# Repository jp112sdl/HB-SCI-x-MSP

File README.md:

# HB-SCI-x-MSP

Ultra-Low-Power 1...4-fach Schließerkontakt-Interface _(basiert auf HM-SCI-3-FM mit MSP430(F2001) Kontaktüberwachung)_.

https://user-images.githubusercontent.com/18190139/149153497-77211921-73f8-495d-b231-c35b709c72b2.mp4

- Code für den MSP430: [main.c](https://github.com/jp112sdl/HB-SCI-x-MSP/blob/master/TI_MSP430/main.c)
- Code für den AVR: [MSP430State.h](https://github.com/jp112sdl/HB-SCI-x-MSP/blob/master/MSP430State.h) und [HB-SCI-x-MSP.ino](https://github.com/jp112sdl/HB-SCI-x-MSP/blob/master/HB-SCI-x-MSP.ino)
  - benötigte Libs: 
    - [Low-Power](https://github.com/rocketscream/Low-Power/)
    - [EnableInterrupt](https://github.com/GreyGnome/EnableInterrupt/)
    - [AskSinPP](https://github.com/pa-pa/AskSinPP)

#### Schaltplan

#### Platine (57x24mm)

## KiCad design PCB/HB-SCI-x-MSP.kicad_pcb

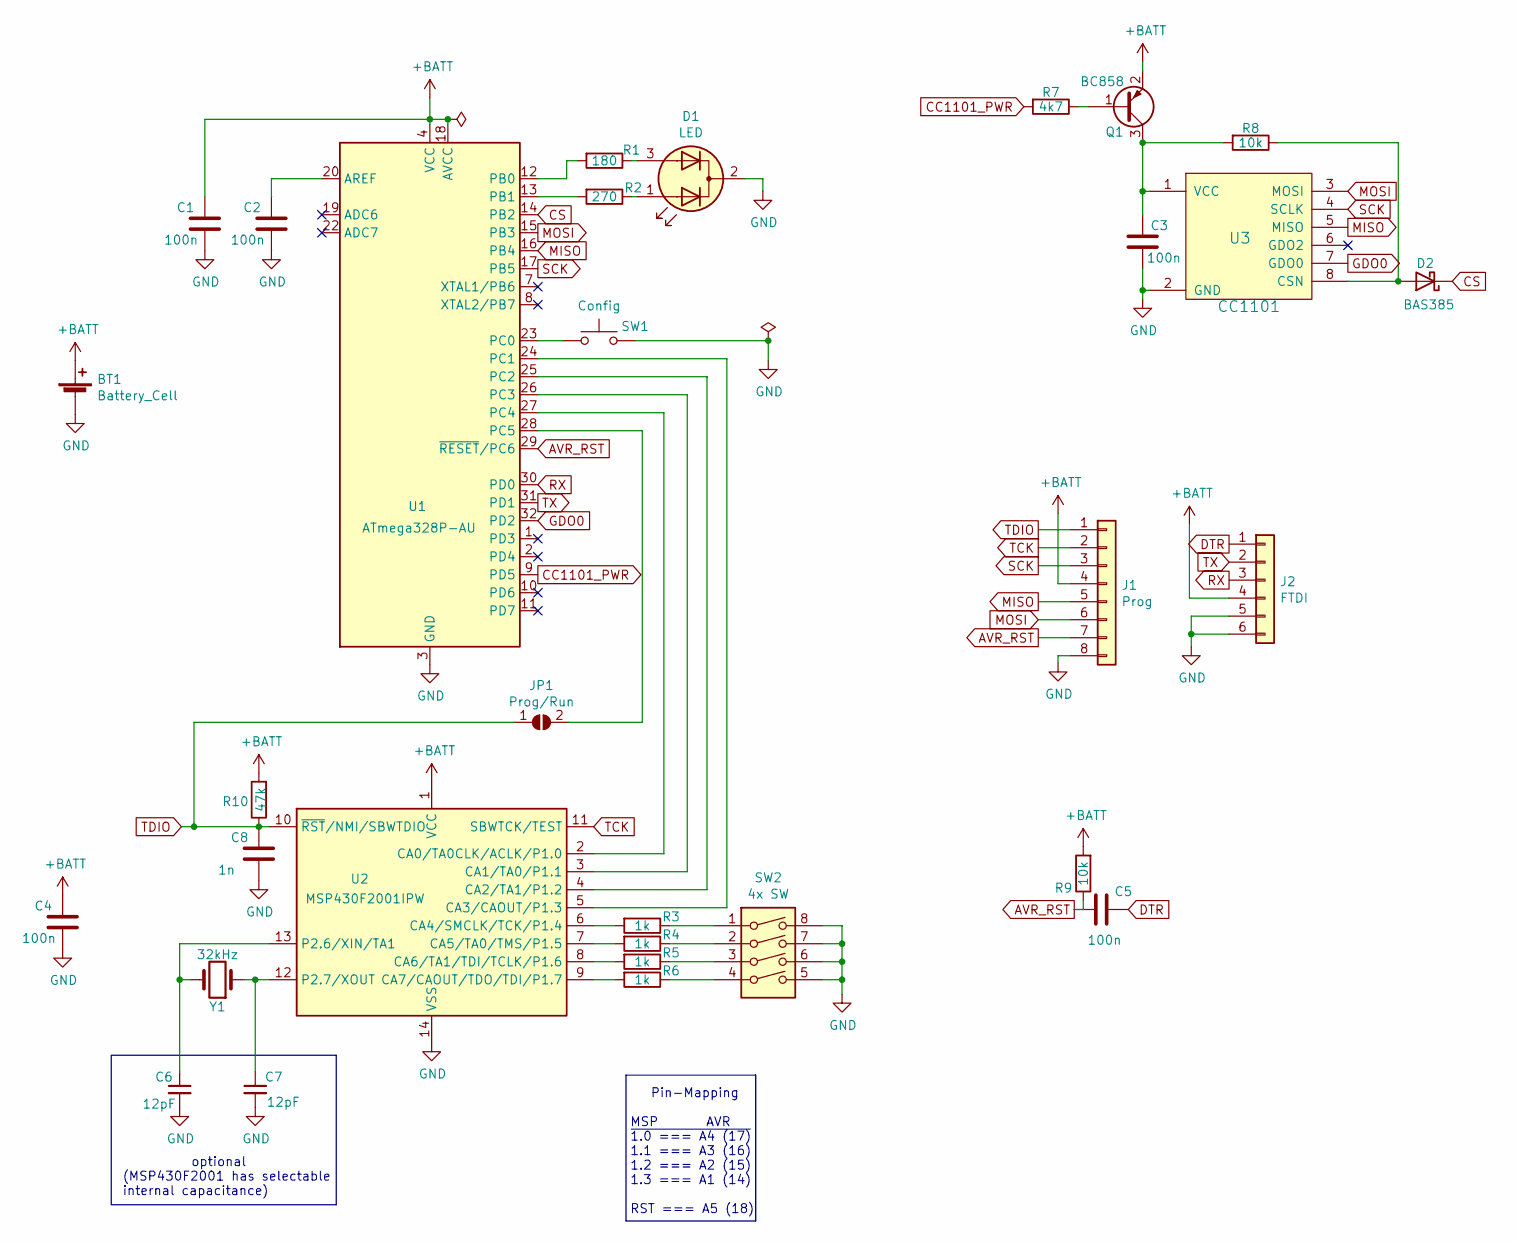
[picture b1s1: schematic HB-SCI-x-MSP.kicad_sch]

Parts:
BT1: Battery_Cell; BatteryHolder_Keystone_1060_1x2032
C1, C2, C3, C4, C5: 100n; C_0805_2012Metric_Pad1.15x1.40mm_HandSolder
C6, C7: 12pF; C_0805_2012Metric_Pad1.15x1.40mm_HandSolder
C8: 1n; C_0805_2012Metric_Pad1.15x1.40mm_HandSolder
D1: LED; LED_D3.0mm-3
D2: BAS385; D_MicroMELF_Hadsoldering
J1: Prog; PinHeader_1x08_P2.00mm_Vertical
J2: FTDI; PinHeader_1x06_P2.54mm_Vertical
JP1: Prog/Run; SolderJumper-2_P1.3mm_Open_Pad1.0x1.5mm
Q1: BC858; SOT-23
R1: 180; R_0805_2012Metric_Pad1.15x1.40mm_HandSolder
R2: 270; R_0805_2012Metric_Pad1.15x1.40mm_HandSolder
R3, R4, R5, R6: 1k; R_0805_2012Metric_Pad1.15x1.40mm_HandSolder
R7: 4k7; R_0805_2012Metric_Pad1.15x1.40mm_HandSolder
R8, R9: 10k; R_0805_2012Metric_Pad1.15x1.40mm_HandSolder
R10: 47k; R_0805_2012Metric_Pad1.15x1.40mm_HandSolder
SW1: Config; SW_SPST_EVQPE1
SW2: 4x SW; PinHeader_2x04_P2.54mm_Vertical
U1: ATmega328P-AU; TQFP-32_7x7mm_P0.8mm
U2: MSP430F2001IPW; TSSOP-14_4.4x5mm_P0.65mm
U3: CC1101; CC1101_Pads
Y1: 32kHz; Crystal_DS26_D2.0mm_L6.0mm_Horizontal

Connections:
+BATT: BT1.1 (+), C1.1, C4.1, J1.4, J2.4, Q1.2 (E), R9.2, R10.2, U1.4 (VCC), U1.6 (VCC), U1.18 (AVCC), U2.1 (VCC)
AVR_RST: C5.2, J1.7, R9.1, U1.29 (~RESET/PC6)
CC1101_PWR: R7.2, U1.9 (PD5)
CS: D2.1 (K), U1.14 (PB2)
DTR: C5.1, J2.1
GDO0: U1.32 (PD2), U3.7 (GDO0)
GND: BT1.2 (-), C1.2, C2.2, C3.2, C4.2, C6.2, C7.2, C8.2, D1.2 (K), J1.8, J2.5, J2.6, SW1.2, SW2.5, SW2.6, SW2.7, SW2.8, U1.3 (GND), U1.5 (GND), U1.21 (GND), U2.14 (VSS), U3.2 (GND)
MISO: J1.5, U1.16 (PB4), U3.5 (MISO)
MOSI: J1.6, U1.15 (PB3), U3.3 (MOSI)
unnamed: C2.1, U1.20 (AREF)
unnamed: C3.1, Q1.3 (C), R8.2, U3.1 (VCC)
unnamed: C6.1, U2.13 (P2.6/XIN/TA1), Y1.2
unnamed: C7.1, U2.12 (P2.7/XOUT), Y1.1
unnamed: D1.1 (A1), R2.1
unnamed: D1.3 (A2), R1.1
unnamed: D2.2 (A), R8.1, U3.8 (CSN)
unnamed: JP1.2 (B), U1.28 (PC5)
unnamed: Q1.1 (B), R7.1
unnamed: R1.2, U1.12 (PB0)
unnamed: R2.2, U1.13 (PB1)
unnamed: R3.1, SW2.1
unnamed: R3.2, U2.6 (CA4/SMCLK/TCK/P1.4)
unnamed: R4.1, SW2.2
unnamed: R4.2, U2.7 (CA5/TA0/TMS/P1.5)
unnamed: R5.1, SW2.3
unnamed: R5.2, U2.8 (CA6/TA1/TDI/TCLK/P1.6)
unnamed: R6.1, SW2.4
unnamed: R6.2, U2.9 (CA7/CAOUT/TDO/TDI/P1.7)
unnamed: SW1.1, U1.23 (PC0)
unnamed: U1.24 (PC1), U2.5 (CA3/CAOUT/P1.3)
unnamed: U1.25 (PC2), U2.4 (CA2/TA1/P1.2)
unnamed: U1.26 (PC3), U2.3 (CA1/TA0/P1.1)
unnamed: U1.27 (PC4), U2.2 (CA0/TA0CLK/ACLK/P1.0)
RX: J2.3, U1.30 (PD0)
SCK: J1.3, U1.17 (PB5), U3.4 (SCLK)
TCK: J1.2, U2.11 (SBWTCK/TEST)
TDIO: C8.1, J1.1, JP1.1 (A), R10.1, U2.10 (~RST/NMI/SBWTDIO)
TX: J2.2, U1.31 (PD1)

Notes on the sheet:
Pin-Mapping MSP AVR ~{1.0 === A4 (17)} 1.1 === A3 (16) 1.2 === A2 (15) 1.3 === A1 (14) RST === A5 (18)
optional (MSP430F2001 has selectable internal capacitance)

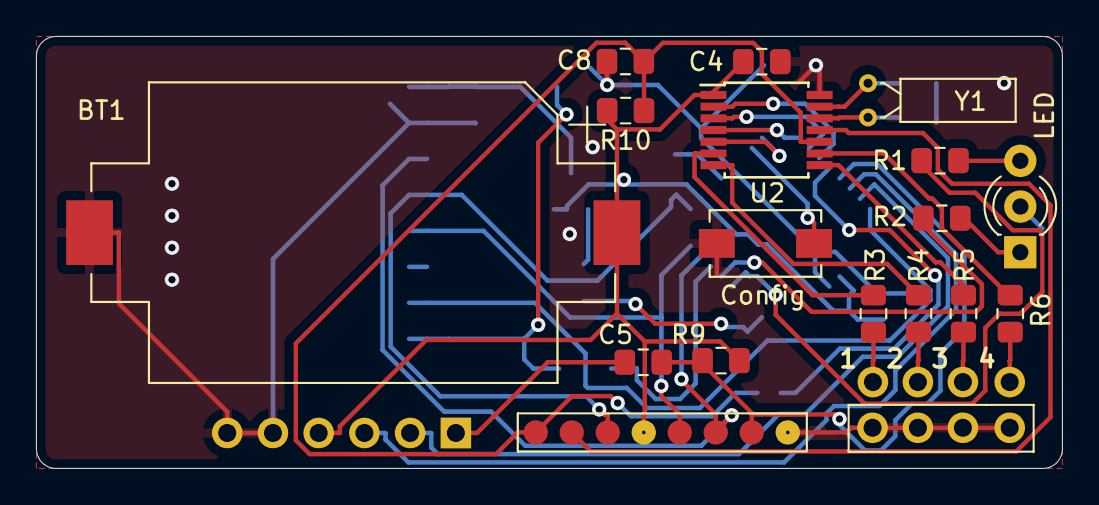
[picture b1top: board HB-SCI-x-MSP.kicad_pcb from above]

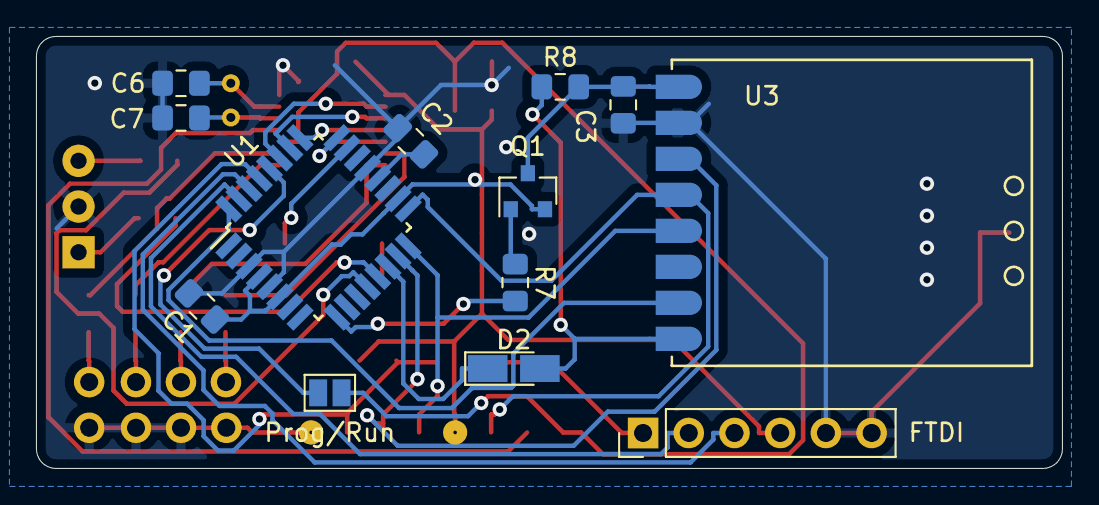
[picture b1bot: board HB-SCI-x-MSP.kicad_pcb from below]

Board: 2 copper layers, 57.0 x 24.0 mm, 31 parts (13 on the bottom side), 38 nets.

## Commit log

2021-08-11 moved file
2021-08-11 add test sketch
2021-08-11 add main sketch
2021-08-11 add license text
2021-08-12 add PCB
2021-08-12 add pcb images
2021-08-12 add schematic image
2021-08-19 update PCB
2021-08-19 renamed identifiers
2021-08-19 fixed final sleep
2021-08-19 stay awake a little bit longer to guarantee long config button press for RESET
2021-08-19 cyclic message has to be sent for all channels
2021-08-27 modified pins according to pcb layout
2021-08-27 update image
2021-09-06 update for 4 channels
2021-09-29 make sure that the AVR is awake
2021-09-29 wake up by interrupt from AVR
2021-09-29 final check for pin changes before going to sleep
2021-09-29 formatting
2021-10-01 reworked comments
2021-11-30 update Kicad 6
2021-12-02 update code to fit atmega168 flash size
2022-01-12 add images
2022-01-12 update kicad
2022-01-12 add blender
